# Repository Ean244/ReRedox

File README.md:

## Terminal v1

Terminal is a ergonomic split keyboard design modified from the [Redox Project](https://github.com/mattdibi/redox-keyboard) by [Mattia Dal Ben (aka u/TiaMaT102)](mailto:matthewdibi@gmail.com).

Key modifications include:

* Replacement of 1.25U keycaps with 1.5U keycaps (which are easier to find / typically found in keycap sets)
* Adding two OLED panels with WPM counter and custom pixel art
* Changing shape of through-holes for the switches the from irregular shapes to regular ones
  * Some board manufacturers do not accept irregular shapes (for me it was JLCPB)
* Adding support stands for a 6 degree tilt

A [sandwich transparent acrylic casing](https://github.com/Ean244/Terminal-Acrylic-Casing) was designed for Terminal v1.

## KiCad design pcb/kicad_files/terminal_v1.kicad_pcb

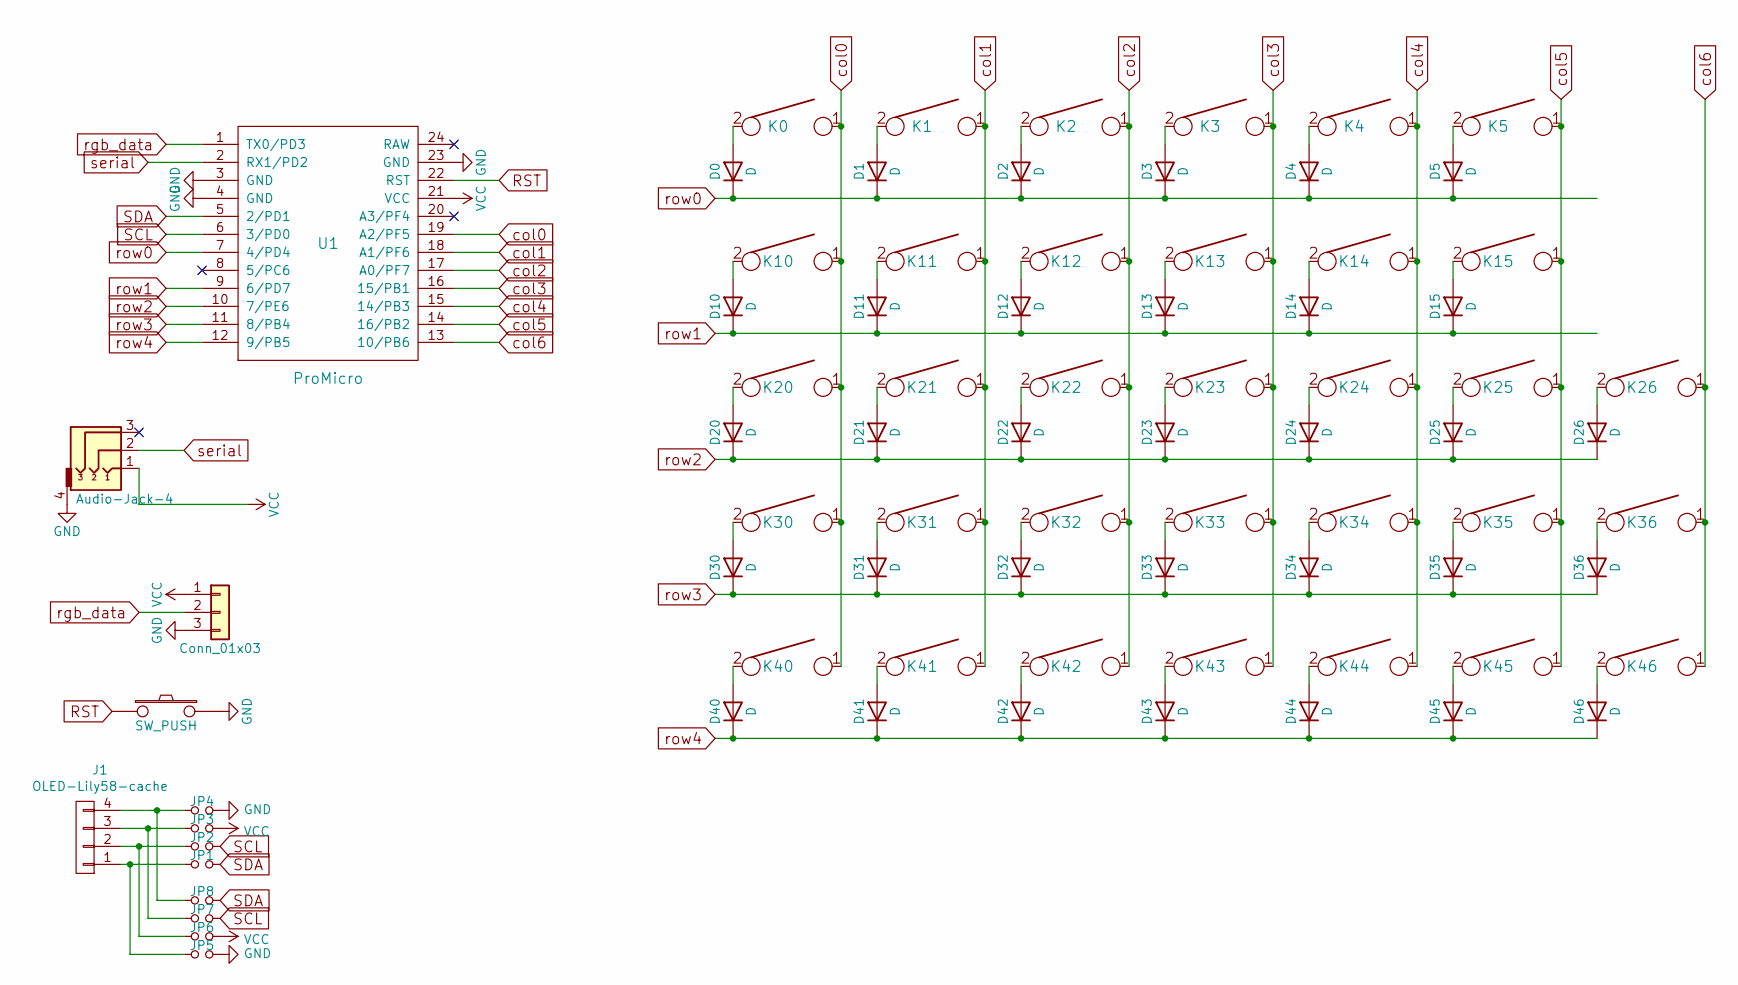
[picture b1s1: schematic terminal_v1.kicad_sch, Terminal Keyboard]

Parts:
D0, D1, D2, D3, D4, D5, D10, D11, D12, D13, D14, D15, D20, D21, D22, D23, D24, D25, D26, D30, D31, D32, D33, D34, D35, D36, D40, D41, D42, D43, D44, D45, D46: D; Diode-dual
J1: OLED-Lily58-cache; OLED_4Pin
JP1, JP2, JP3, JP4, JP5, JP6, JP7, JP8: Jumper_NO_Small; Jumper
K0, K1, K2, K3, K4, K5, K10, K11, K12, K13, K14, K15, K20, K21, K22, K23, K24, K25, K26, K30, K31, K32, K33, K34, K35, K36, K40, K41, K42, K43, K44, K45, K46: KEYSW; SW_MX_reversible
U1: ProMicro; ArduinoProMicro

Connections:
GND: JP4.2, JP5.2, U1.3 (GND), U1.4 (GND), U1.23 (GND); also elsewhere on the board
unnamed: D0.2 (A), K0.2
unnamed: D1.2 (A), K1.2
unnamed: D2.2 (A), K2.2
unnamed: D3.2 (A), K3.2
unnamed: D4.2 (A), K4.2
unnamed: D5.2 (A), K5.2
unnamed: D10.2 (A), K10.2
unnamed: D11.2 (A), K11.2
unnamed: D12.2 (A), K12.2
unnamed: D13.2 (A), K13.2
unnamed: D14.2 (A), K14.2
unnamed: D15.2 (A), K15.2
unnamed: D20.2 (A), K20.2
unnamed: D21.2 (A), K21.2
unnamed: D22.2 (A), K22.2
unnamed: D23.2 (A), K23.2
unnamed: D24.2 (A), K24.2
unnamed: D25.2 (A), K25.2
unnamed: D26.2 (A), K26.2
unnamed: D30.2 (A), K30.2
unnamed: D31.2 (A), K31.2
unnamed: D32.2 (A), K32.2
unnamed: D33.2 (A), K33.2
unnamed: D34.2 (A), K34.2
unnamed: D35.2 (A), K35.2
unnamed: D36.2 (A), K36.2
unnamed: D40.2 (A), K40.2
unnamed: D41.2 (A), K41.2
unnamed: D42.2 (A), K42.2
unnamed: D43.2 (A), K43.2
unnamed: D44.2 (A), K44.2
unnamed: D45.2 (A), K45.2
unnamed: D46.2 (A), K46.2
unnamed: J1.1, JP1.1, JP5.1
unnamed: J1.2, JP2.1, JP6.1
unnamed: J1.3, JP3.1, JP7.1
unnamed: J1.4, JP4.1, JP8.1
RST: U1.22 (RST); also elsewhere on the board
SCL: JP2.2, JP7.2, U1.6 (3/PD0)
SDA: JP1.2, JP8.2, U1.5 (2/PD1)
VCC: JP3.2, JP6.2, U1.21 (VCC); also elsewhere on the board
col0: K0.1, K10.1, K20.1, K30.1, K40.1, U1.19 (A2/PF5)
col1: K1.1, K11.1, K21.1, K31.1, K41.1, U1.18 (A1/PF6)
col2: K2.1, K12.1, K22.1, K32.1, K42.1, U1.17 (A0/PF7)
col3: K3.1, K13.1, K23.1, K33.1, K43.1, U1.16 (15/PB1)
col4: K4.1, K14.1, K24.1, K34.1, K44.1, U1.15 (14/PB3)
col5: K5.1, K15.1, K25.1, K35.1, K45.1, U1.14 (16/PB2)
col6: K26.1, K36.1, K46.1, U1.13 (10/PB6)
rgb_data: U1.1 (TX0/PD3); also elsewhere on the board
row0: D0.1 (K), D1.1 (K), D2.1 (K), D3.1 (K), D4.1 (K), D5.1 (K), U1.7 (4/PD4)
row1: D10.1 (K), D11.1 (K), D12.1 (K), D13.1 (K), D14.1 (K), D15.1 (K), U1.9 (6/PD7)
row2: D20.1 (K), D21.1 (K), D22.1 (K), D23.1 (K), D24.1 (K), D25.1 (K), D26.1 (K), U1.10 (7/PE6)
row3: D30.1 (K), D31.1 (K), D32.1 (K), D33.1 (K), D34.1 (K), D35.1 (K), D36.1 (K), U1.11 (8/PB4)
row4: D40.1 (K), D41.1 (K), D42.1 (K), D43.1 (K), D44.1 (K), D45.1 (K), D46.1 (K), U1.12 (9/PB5)
serial: U1.2 (RX1/PD2); also elsewhere on the board

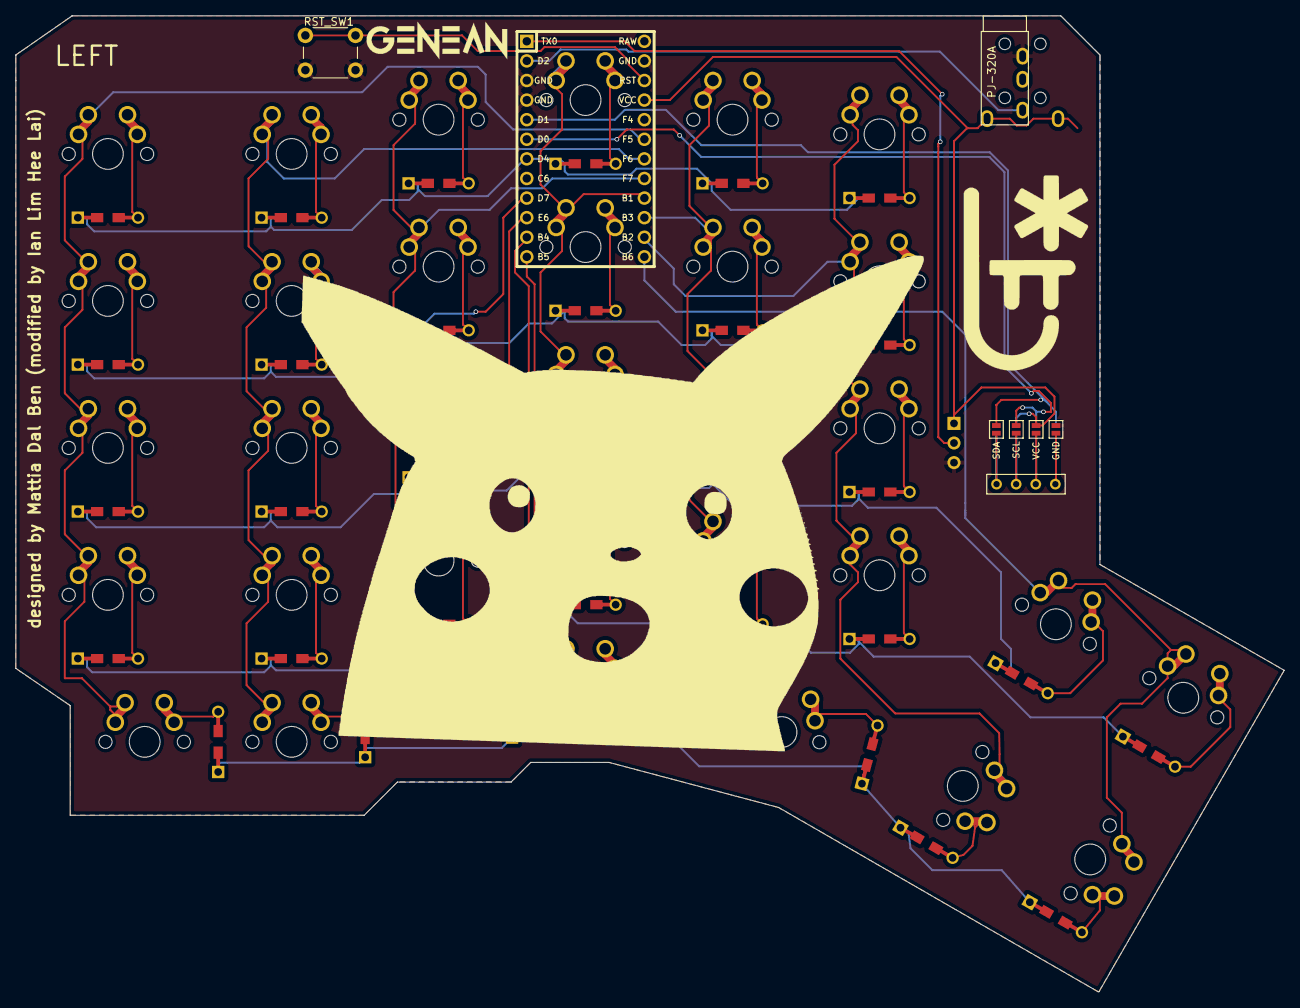
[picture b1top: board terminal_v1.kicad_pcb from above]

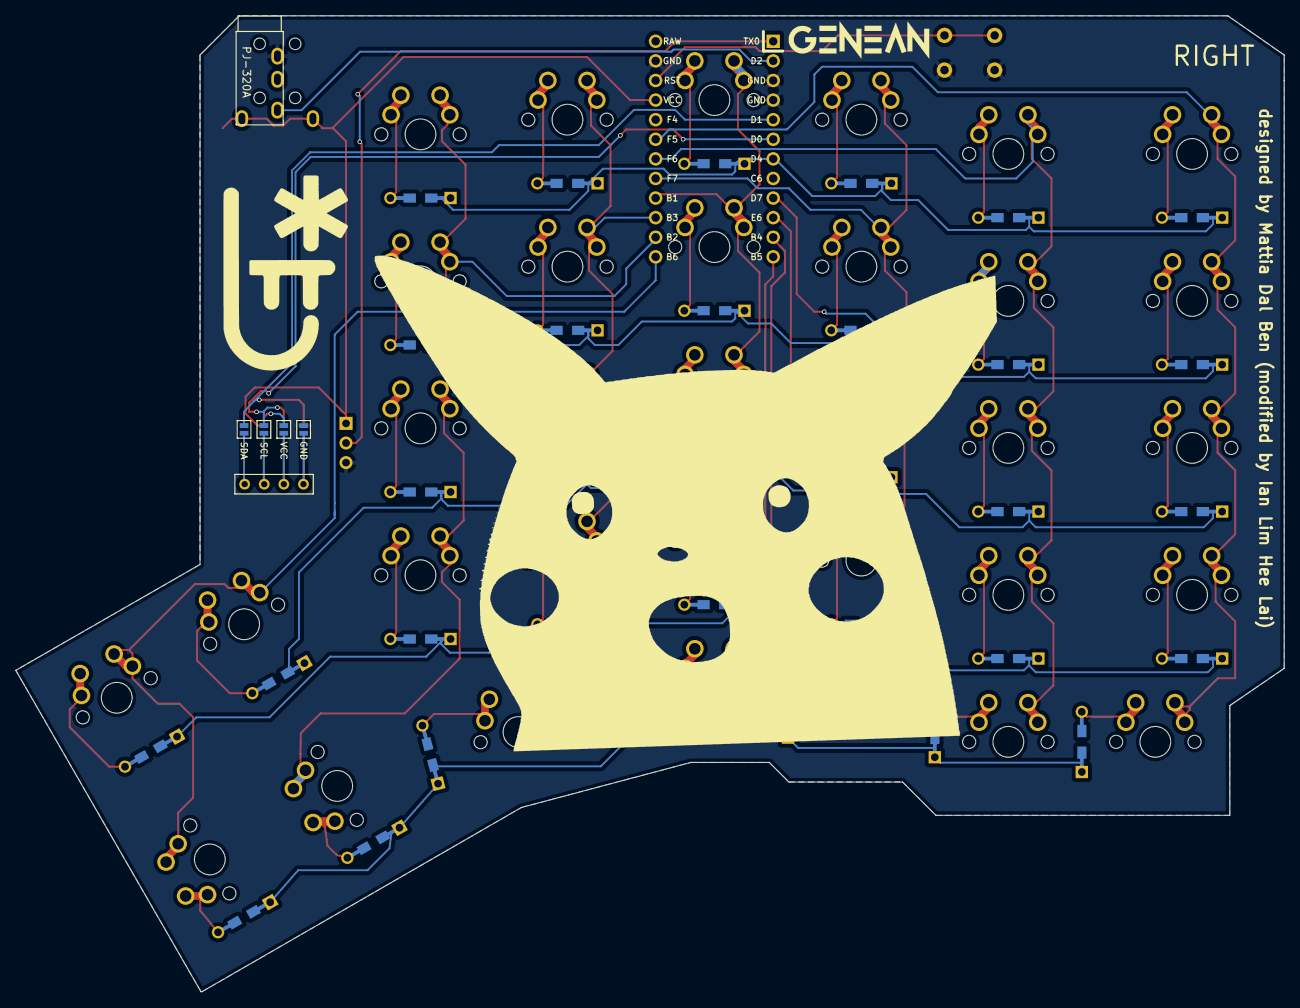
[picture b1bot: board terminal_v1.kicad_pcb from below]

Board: 2 copper layers, 164.4 x 126.5 mm, 79 parts (4 on the bottom side), 56 nets.

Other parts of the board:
RGB_STRIP1: Conn_01x03; Pin_Header_Straight_1x03_Pitch2.54mm
RST_SW1: SW_PUSH; SW_PUSH_6mm_h4.3mm
TRRS1: Audio-Jack-4; TRRS-PJ-320A-dual

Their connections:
GND: RGB_STRIP1.3, RST_SW1.2, TRRS1.4; also elsewhere on the board
RST: RST_SW1.1; also elsewhere on the board
VCC: RGB_STRIP1.1, TRRS1.1; also elsewhere on the board
rgb_data: RGB_STRIP1.2; also elsewhere on the board
serial: TRRS1.2; also elsewhere on the board

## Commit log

2020-09-04 Enlarge usb ports
2020-09-04 Fixed mirroring issues
2021-01-16 Final edit
2021-01-16 test
2021-01-16 Added oled
2021-01-16 update netsat
2021-01-17 Completed pcb routing
2021-01-17 Minor
2021-01-17 Added pika :)
2021-01-18 shifted keys to 1.5u
2022-08-07 updated license
2022-08-07 rename
2022-08-07 added link
2022-08-07 included oled updates
2022-11-15 Added gitignore
2022-11-15 removed legacy files

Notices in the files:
pcb/kicad_files/terminal_v1.kicad_sch:
MIT License
